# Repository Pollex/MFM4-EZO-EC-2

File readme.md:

# MFM Atlas Scientific Module x2

This sensor module carries a Atlas-Scientific EZO-EC board and isolates and multiplexes the signal line to two SMA connectors for probes.

This sensor module contains a USB-C port for easier configuration and calibration of the different probes. This also allows the module to be used standalone in an ESD protected environment.

## Hardware

A single MFM V4 has two sensor module slots with about 9mm clearance between slot 1 and 2.

### Parts

Most if not all parts in kicad have a datasheet attached to them. Select the part in the Schematic Editor and press the 'd' key.

## Firmware

To be designed

## Configuration interface

To be designed

# RIOT OS
Clone riot os 2024.07 and apply patch 001

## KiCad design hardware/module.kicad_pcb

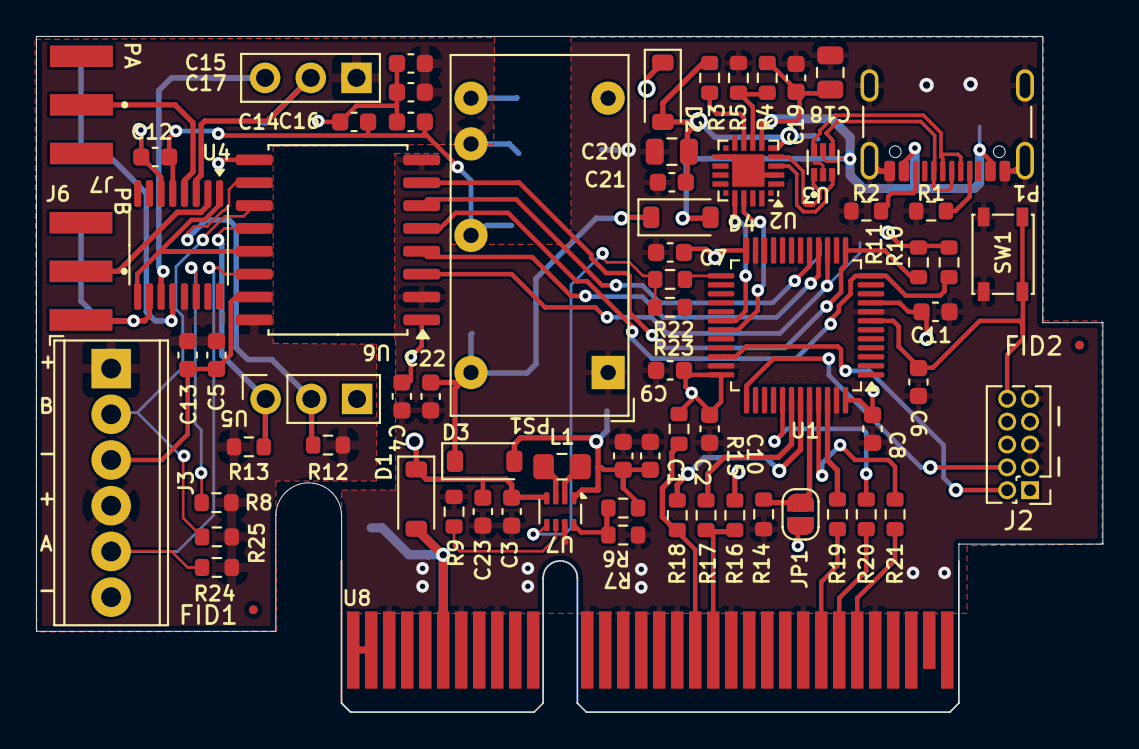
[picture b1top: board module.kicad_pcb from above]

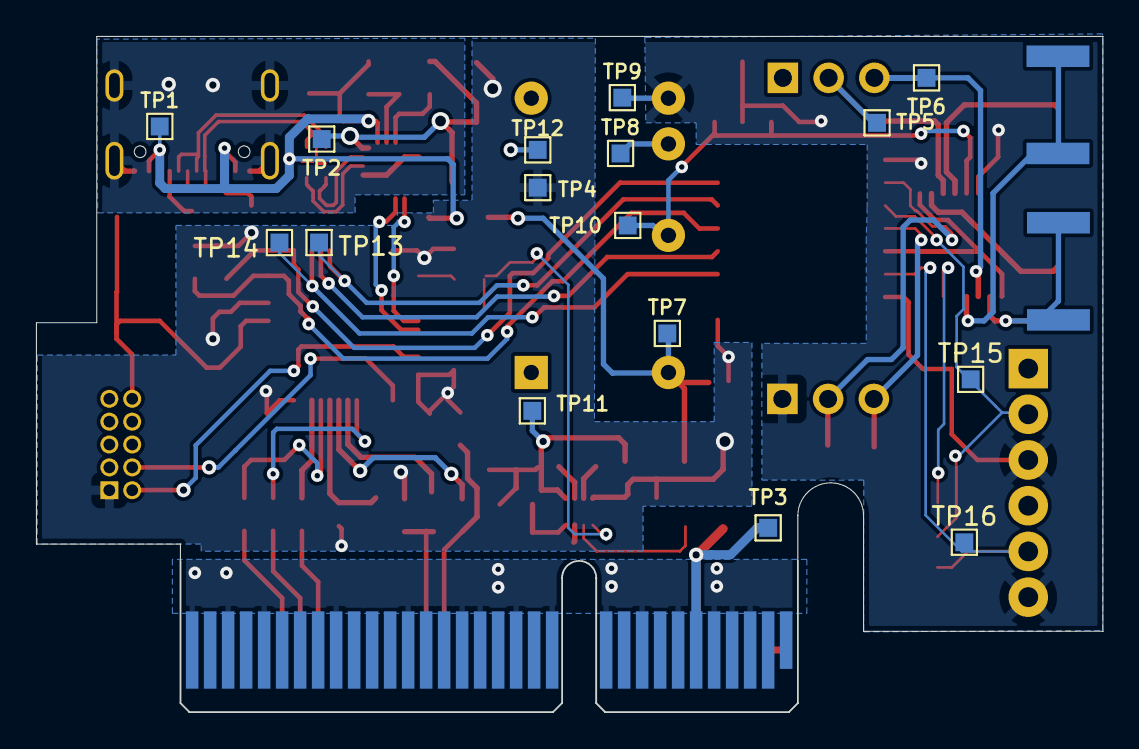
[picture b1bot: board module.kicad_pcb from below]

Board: 2 copper layers, 59.2 x 37.5 mm, 87 parts (16 on the bottom side), 59 nets.

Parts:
C1, C11, C16, C17, C19, C21: 4u7; C_0603_1608Metric
C2, C22, C23: 10u; C_0603_1608Metric
C3: 22u; C_0603_1608Metric
C4, C5, C6, C7, C8, C9, C10, C12, C13, C14, C15: 100n; C_0603_1608Metric
C18, C20: 47u; C_0805_2012Metric
D1, D2, D3, D4: MBR0520LT1G; D_SOD-123
FID1, FID2: Fiducial; Fiducial_0.5mm_Mask1mm
J2: GPHD-2X05; PinHeader_2x05_P1.27mm_Vertical
J3: 1725698; TerminalBlock_Phoenix_MPT-0,5-6-2.54_1x06_P2.54mm_Horizontal
J6, J7: CON-SMA-EDGE-S; RFSOLUTIONS_CON-SMA-EDGE-S
JP1: BOOT; SolderJumper-2_P1.3mm_Open_RoundedPad1.0x1.5mm
L1: LPWI201208S1R0T; L_0805_2012Metric_Pad1.15x1.40mm_HandSolder
P1: USB4105-GF-A; USB_C_Receptacle_GCT_USB4105-xx-A_16P_TopMnt_Horizontal
PS1: IA0505D; Converter_DCDC_XP_POWER-IAxxxxD_THT
R1, R2, R24, R25: 5k2; R_0603_1608Metric
R3, R14: 1k; R_0603_1608Metric
R4: 22k1; R_0603_1608Metric
R5: 47k5; R_0603_1608Metric
R6: 806k; R_0603_1608Metric
R7: 91k; R_0603_1608Metric
R8, R9, R23: 10k; R_0603_1608Metric
R10, R11, R12, R13: 3k; R_0603_1608Metric
R15, R16: 2K2; R_0603_1608Metric
R17, R18, R19, R20, R21, R22: 0R; R_0603_1608Metric
SW1: PTS810SJG250SMTRLFS; SW_SPST_PTS810
TP1, TP2, TP3, TP4, TP5, TP6, TP7, TP8, TP9, TP10, TP11, TP12, TP13, TP14, TP15, TP16: TestPoint; TestPoint_Pad_1.0x1.0mm
U1: STM32L010C6T6; LQFP-48_7x7mm_P0.5mm
U2: CP2102N-A02-GQFN20; SiliconLabs_QFN-20-1EP_3x3mm_P0.5mm_EP1.8x1.8mm
U3: USBLC6-2P6; SOT50P160X60-6N
U4: TMUX6236PWR; TSSOP-16_4.4x5mm_P0.65mm
U5: EZO-EC™; EZO_EZ
U6: ISO1644DWR; SOIC-16W_7.5x10.3mm_P1.27mm
U7: TPS631000DRLR; SOT-583-8
U8: PCIEx4; BUS_PCIexpress_x4

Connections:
3V3: C3.1, C4.1, C7.1, C8.1, C9.1, C10.1, C11.1, C23.1, D1.1 (K), D2.1 (K), J2.1, JP1.2 (B), R10.2, R11.2, R15.1, R16.1, TP4.1, U1.9 (VDDA), U1.24 (VDD), U1.36 (VDD), U1.48 (VDD), U6.1 (VCC1), U7.4 (Vin)
+5V: C1.1, C2.1, D3.2 (A), R6.2, TP11.1, U7.1 (Vout)
+5V_ISO: C5.1, C13.1, C15.1, C17.1, J3.1, J3.4, PS1.5 (+Vout), R8.2, R12.1, R13.1, R24.2, R25.2, TP8.1, U4.13 (VDD), U5.6 (VCC), U6.16 (VCC2)
-5V_ISO: C12.1, C14.2, C16.2, PS1.4 (-Vout), TP10.1, U4.5 (VSS)
/BOOST_EN: R22.1, R23.1, U7.5 (EN)
/BOOT: JP1.1 (A), R14.2, U1.44 (BOOT0)
/CP_N: U2.5 (D-), U3.1
/CP_P: U2.4 (D+), U3.3
/DQ_TEMP_A: TP14.1, U1.15 (PA5), U6.3 (SDA1)
/DQ_TEMP_A_ISO: J3.5, R24.1, TP16.1, U6.14 (SDA2)
/DQ_TEMP_B: TP13.1, U1.17 (PA7), U6.6 (SCL1)
/DQ_TEMP_B_ISO: J3.2, R25.1, TP15.1, U6.11 (SCL2)
/I2C_SCL: R16.2, R17.1, U8.B19
/I2C_SDA: R15.2, R18.1, U8.B18
/LPUART1_RX: R11.1, U1.13 (PA3), U6.7 (OUT)
/LPUART1_TX: R10.1, U1.12 (PA2), U6.5 (INB)
/MOD_ID1: R19.1, U8.B25
/MOD_ID2: R20.1, U8.B26
/MOD_ID3: R21.1, U8.B27
/NRST: C6.1, J2.10, SW1.2 (B), U1.7 (NRST)
/PRB_SEL: U4.1 (SEL1), U4.9 (SEL2), U6.13 (OUTA)
/PRB_SEL_MCU: U1.16 (PA6), U6.4 (INA)
/SWCLK: J2.4, U1.37 (PA14)
/SWDIO: J2.2, U1.34 (PA13)
/SensorConnector/VBUS: U8.A1, U8.A2, U8.B1, U8.B2
/SensorConnector/VREF: U8.A8, U8.B8
/UART2_RX: U1.31 (PA10), U2.18 (TXD)
/UART2_TX: U1.30 (PA9), U2.17 (RXD)
/USB_N: P1.A7 (D-), P1.B7 (D-), U3.6
/USB_P: P1.A6 (D+), P1.B6 (D+), U3.4
CP2102_3V3: C20.1, C21.1, D2.2 (A), R3.2, TP2.1, U2.6 (VDD)
GND: C1.2, C2.2, C3.2, C4.2, C6.2, C7.2, C8.2, C9.2, C10.2, C11.2, C18.2, C19.2, C20.2, C21.2, C22.2, C23.2, J2.3, J2.5, J2.9, P1.A1 (GND), P1.A12 (GND), P1.B1 (GND), P1.B12 (GND), P1.S1 (SHIELD), PS1.1 (-Vin), R1.2, R2.2, R5.1, R7.1, R9.2, R14.1, R23.2, SW1.1 (A), TP12.1, U1.8 (VSSA), U1.23 (VSS), U1.35 (VSS), U1.47 (VSS), U2.3 (GND), U2.12 (GND), U2.21 (GND), U3.2, U6.2 (GND1), U6.8 (GND1), U7.7 (GND), U8.A3, U8.A4, U8.A5, U8.A7, U8.A9, U8.A11, U8.A12, U8.A14, U8.A16, U8.A17, U8.A18, U8.A19, U8.A20, U8.A24, U8.A26, U8.A28, U8.A30, U8.A32, U8.B3, U8.B5, U8.B7, U8.B9, U8.B12, U8.B14, U8.B16, U8.B17, U8.B20, U8.B24, U8.B28
GND_ISO: C5.2, C12.2, C13.2, C14.1, C15.2, C16.1, C17.2, J3.3, J3.6, PS1.6 (0V), TP9.1, U4.6 (GND), U5.3 (GND), U6.9 (GND2), U6.15 (GND2)
unnamed: C22.1, D3.1 (K), D4.1 (K), PS1.3 (+Vin), TP7.1
unnamed: P1.A5 (CC), R1.1
unnamed: P1.B5 (VCONN), R2.1
unnamed: R20.2, U1.41 (PB5)
unnamed: R17.2, U1.42 (PB6)
unnamed: R18.2, U1.43 (PB7)
unnamed: R21.2, U1.45 (PB8)
unnamed: R19.2, U1.46 (PB9)
unnamed: R22.2, U1.25 (PB12)
unnamed: R4.1, R5.2, U2.8 (VBUS)
unnamed: R3.1, U2.9 (~RST)
unnamed: TP5.1, U4.3 (D1), U5.5 (PRB)
unnamed: TP6.1, U4.11 (D2), U5.4 (PRB)
unnamed: R8.1, U4.14 (EN)
unnamed: J6.1, U4.2 (S1A)
unnamed: J7.1, U4.4 (S1B)
unnamed: J6.G1, J6.G2, J6.G3, J6.G4, U4.10 (S2A)
unnamed: J7.G1, J7.G2, J7.G3, J7.G4, U4.12 (S2B)
unnamed: R13.2, U5.1 (RX/SCL), U6.12 (OUTB)
unnamed: R12.2, U5.2 (TX/SDA), U6.10 (INC)
unnamed: R6.1, R7.2, U7.8 (FB)
unnamed: L1.1, U7.3 (LX1)
unnamed: L1.2, U7.2 (LX2)
unnamed: R9.1, U7.6 (MODE)
USB_VBUS: C18.1, C19.1, D4.2 (A), P1.A4 (VBUS), P1.A9 (VBUS), P1.B4 (VBUS), P1.B9 (VBUS), R4.2, TP1.1, U2.7 (VREGIN), U3.5
VSensor: D1.2 (A), TP3.1, U8.A6, U8.B6

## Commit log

2024-07-10 Add preliminary readme
2024-09-10 feat: saul write IO, Read EC into buf
2024-10-11 feat(ezoec): read
2024-10-14 Update PCB module design
2024-10-14 feat: add ds18b20 support
2024-10-16 chore(ezoec): disable debug, clear RB before write
2024-10-16 feat: calibration import export
2024-10-28 Feat: calibration stabilize before continue
2024-10-31 implement i2c slave, commands, measurements and provisioning procedure
2024-10-31 Fix: i2c use msg to main thread
2024-10-31 feat: disable ezoec led during provisioning
2024-11-01 Fix: i2c addr calculation, update diagram
2025-04-14 feat: new shell commands chore: remove saul pins chore: add compile time FW_VERSION docs: add calibration interpolated graphs
2025-06-30 fix(i2c): not initializing correctly in slot 2 This commit also fixes the Time-To-Ready of I2C from 500ms to <1ms.
2025-06-30 chore: update board config for newer RIOT
2025-08-22 fix: incorrect i2c speed
2025-08-22 feat: riot: i2c slave
2025-12-08 chore: add fab dir to ignore
2026-03-09 Add submodule for RIOT at 2026.01
2026-03-09 refactor: use mfm_comm module
2026-03-09 chore: fix zero init, increase measurement_time
2026-03-09 feat: add mfm comm errors
2026-03-13 refactor: improve threading and error handling in ezoec driver
    Replace polling-based ringbuffer with thread-safe ring buffer (tsrb) and
    use thread flags for efficient UART rx synchronization. Add mutex protection
    for readline operations and improve error propagation in mfm_comm and sensor
    initialization paths. Implement set_k shell command and increase message
    queue capacity for better reliability.
2026-03-16 fix: tsrf buf ^2, out = 0 on error
2026-03-17 feat: conditional probe calib/usage
2026-03-17 chore: ignore RIOT as dirty
2026-04-02 wip: improvements
2026-04-14 fix: enforce 750ms for ds18b20 refactor: merge to main.c
2026-05-12 fix(mfm_comm): return app_error byte on second read_error_status
    When MFM_COMM_ERR_APP is asserted, the protocol expects the host to read
    once for the generic error byte and a second time for the application-
    specific payload. The second read was returning comm->error again, so
    the MFM master never saw the actual per-probe error bitmap assembled in
    main.c (ERR_TEMP_A_TRIGGER, ERR_CONDUCTIVITY_A, etc.).
2026-05-12 fix(ezoec): _int_to_string handles k=0 and all precisions
    The helper previously skipped the digit-writing loop when k==0, returning
    a pointer to the static buffer's NUL terminator. Any caller invoking
    ezoec_set_k(0) would have sent "K,\r" and received *ER from the EZO.
    Also fixes precision > 1 with k < 10^(precision-1): the loop only inserted
    the decimal point when reaching `precision` digits of input, so values
    like (k=1, precision=3) returned "1" instead of "0.001". The do-while
2026-05-12 refactor(provisioning): use min-max spread instead of variance for stability
    The variance computation mixed signed and unsigned types and squared
    deviations into a uint32_t, which would overflow for high-K-probe
    readings near saline-range conductivities (e.g. 100k uS² already
    overflows int32 squared math).
    Replace with a straightforward min-max spread across the rolling window
    and compare against the tolerance directly. Simpler, intuitive, and
2026-05-12 fix(ezoec): return -ENODEV when init detects a non-EC device
    ezoec_init previously returned the positive byte count from the version
    read on both "response too short" and "device is not EC" branches.
    Callers (e.g. sensors_init in main.c) treat any negative return as
    failure, so a non-EC EZO module on the UART would silently look like
    a healthy init. Return -ENODEV in both cases.
2026-05-12 fix(ezoec): bounds-check cal_export against calibration array
    The Export loop memcpy'd into cal->line[line] before checking the
    EZOEC_CALIBRATION_MAX_LINES bound. If the EZO ever returned more lines
    than expected before *DONE (or the constants drift), the trailing
    iteration writes past the array. Also clamp the per-line memcpy size
    to EZOEC_CALIBRATION_LINE_LENGTH so a long response can't spill into
    the next slot.
2026-05-12 fix(ezoec): guard vsnprintf return in writeline/cmd
    vsnprintf returns the number of bytes that would be written, not the
    number actually written. If a format ever truncates (or returns
    negative on encoding error), the next line `txbuf[len++] = '\r'` writes
    out of bounds into BSS, corrupting adjacent statics. Bail with
    -EOVERFLOW on both overflow and encoding error.
2026-05-12 fix(ezoec): harden ezoec_measure parser against unexpected output
    The parser blindly added (*ptr - '0') to a uint32_t accumulator. A
    comma — as appears in multi-field output like "100,54" when TDS/SAL/SG
    is enabled — yields -4 and wraps the accumulator into garbage. Now
    stop at the first non-digit/non-dot character, reject double-dot input,
    and require at least one digit. Behaviour for EC-only output ("1413"
    or "1.413") is unchanged.
2026-05-12 fix(ezoec): pass caller buffer size into ezoec_cmd
    Previously ezoec_cmd hardcoded RX_MAX_LINE_LEN (42 bytes) as the read
    length regardless of the caller's actual buffer. Callers with smaller
    buffers — version[15] in ezoec_init, rxBuffer[13] in ezoec_cal_export
    — could be overflowed by a long EZO response, corrupting the stack.
    Add an out_len parameter and propagate it through ezoec_readline.
    All call sites pass sizeof(buf) for the buffered cases or 0 for the
2026-05-12 refactor: consolidate measurement into shared perform_measurement()
    Extract the EC + temperature measurement flow into a single helper used
    by both the shell `measure` command and the I2C MSG_DO_MEASURE handler,
    so they no longer drift. The shell path now initializes sensors and
    respects per-probe calibration gating; the I2C path drops its 850 ms
    blocking wait by triggering temperature conversions before the slower
    EC read so they overlap.
